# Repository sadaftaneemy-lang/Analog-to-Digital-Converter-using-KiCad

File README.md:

# Analog to Digital Converter using KiCad

## 📌 Self-Initiated Project
This is a self-initiated project created to explore and apply concepts in electronics through hands-on design and simulation

## What is KiCad ??
KiCad is a free, open-source Electronic Design Automation (EDA) tool used to design electronic circuits and Printed Circuit Boards (PCBs). 

## What is an AC to DC Converter 
An Analog to Digital Converter (ADC)  is a circuit that converts a continuous analog signal (like temperature, sound, voltage, sensor output) into a digital binary number that digital systems can process

## 🔰 Applications
An ADC is used wherever real-world analog signals must be converted into digital form for processing by digital systems like microcontrollers, DSPs, processors, or computers.

1. Audio Processing
   Microphones produce analog signals.

ADC converts:
- Voice
- Music
- Sound waves, into digital data.

Which is used  in:
- Mobile phones
- Voice recorders
- Bluetooth devices
- Digital audio systems

2. Medical equipments
  Biomedical signals are analog.

ADC is used in:
- ECG
- EEG
- Patient monitoring systems
- Digital thermometers

## 🤖 Advantages
❉ ADCs help digital systems accurately interpret continuously varying real-world signals such as temperature, sound, pressure, and light.

❉ They reduce the effect of external noise because digital signals are more reliable and less sensitive to interference than analog signals.

❉ ADCs make it possible to store analog information in digital memory devices for long-term usage and analysis.

❉ They enable fast processing of signals using microprocessors, DSPs, and embedded controllers.

❉ ADCs improve system flexibility because digital data can be easily modified, encrypted, compressed, or transmitted over networks

## 🛰️ ADC Flow
1. Analog input is applied
2. ADC samples the signal
3. Quantizes it into levels
4. Produces binary output

# 🔋 KiCad 
KiCad is an open-source EDA (Electronic Design Automation) software used for:
1. Schematic design
2. PCB layout
3. Simulation
4. Gerber generation
5. 3D PCB visualization

## 🔗🔗 Installation
I referred to this video for setup:
- [https://youtu.be/JZitbgEbCHU?si=QlpFLPeTkP8un1ju]

# 📐 About the project
This project presents the design and implementation of an AC to DC Converter PCB using KiCad. The circuit converts an alternating current (AC) input into a regulated direct current (DC) output using a bridge rectifier configuration, filtering capacitor, resistor network, and LED indication circuit.

The project was designed completely in KiCad, including:

   - Schematic design
   - PCB layout
   - Routing
   - Footprint assignment
   - Ground plane generation
   - 3D visualization preparation

This project demonstrates basic power electronics concepts along with practical PCB design workflow using an industry-standard open-source EDA tool.

## 🧩 Components Used

✮ D1–D4	1N4007 Rectifier Diodes

✮ C1	Filter Capacitor

✮ R1, R2	Resistors

✮ D5	LED Indicator

✮ J1	AC Input Terminal

✮ J2	DC Output Terminal

## 🔌 Working Principle

The AC voltage is applied through the input connector. The four diodes connected in bridge rectifier configuration convert the alternating current into pulsating DC. The capacitor filters the ripple content and provides a smoother DC output voltage. The resistor and LED combination acts as an output power indicator. The final DC output is obtained at the output terminal connector.

## 📂 Project Workflow

➤ Schematic Design

➤ ERC Verification

➤ Footprint Assignment

➤ PCB Layout Design

➤ Routing and Ground Fill

➤ DRC Check

➤ Gerber File Generation

## 🎯 Applications

⚡ Power supply circuits

⚡ Embedded systems

⚡ Educational electronics projects

⚡ PCB design practice

⚡ Low-power DC supply applications

## 🚀 Learning Outcomes

Through this project, the following concepts were learned:

- PCB designing using KiCad
- Schematic capture
- Component footprint mapping
- PCB routing techniques
- Bridge rectifier operation
- Power supply circuit fundamentals
- Design Rule Check (DRC) and ERC validation

## 📸 Project Images

**1. Schematic screenshot**

**2. PCB layout screenshot**

## Acknowledgement

This project was developed for learning and practice purposes to understand PCB design flow and AC to DC conversion using KiCad. External tutorials and documentation were referred to during installation and project development.

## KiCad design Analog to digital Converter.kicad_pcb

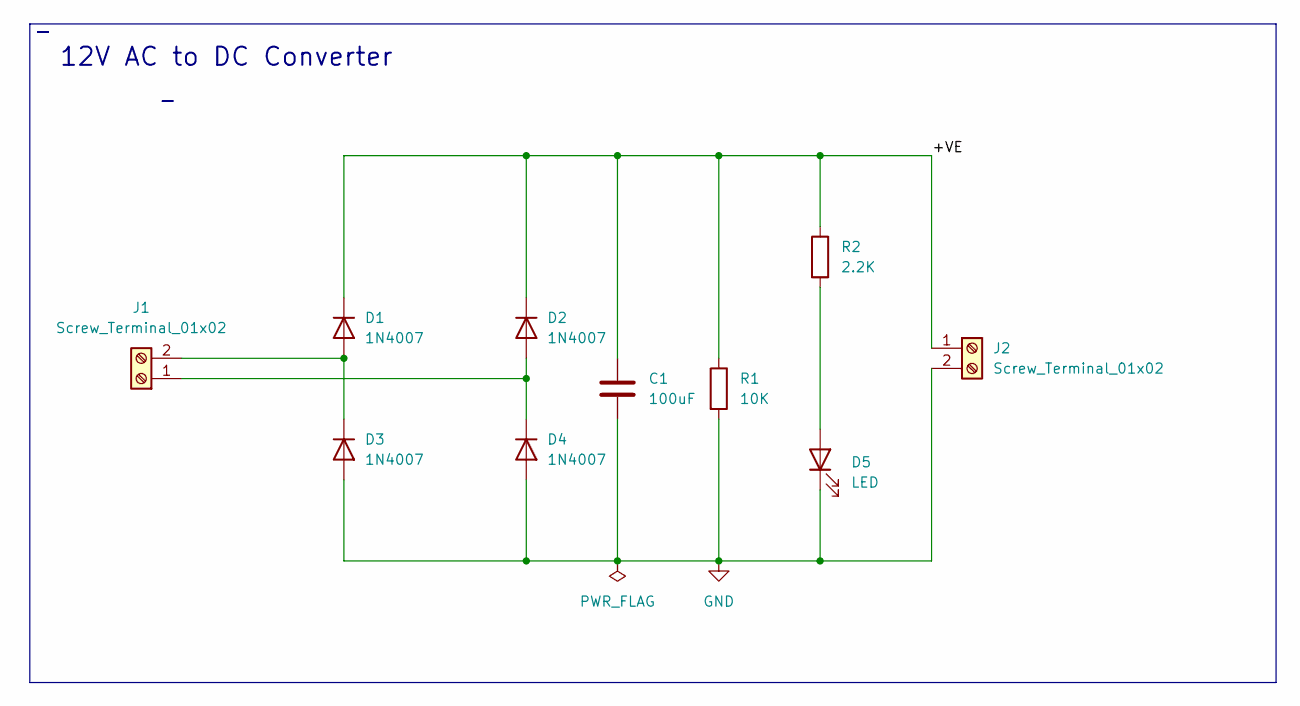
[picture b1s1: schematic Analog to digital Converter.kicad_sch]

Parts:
C1: 100uF; C_Radial_D8.0mm_H11.5mm_P3.50mm
D1, D2, D3, D4: 1N4007; D_DO-41_SOD81_P10.16mm_Horizontal
D5: LED; LED_D5.0mm
J1, J2: Screw_Terminal_01x02; TerminalBlock_MaiXu_MX126-5.0-02P_1x02_P5.00mm
R1: 10K; R_Axial_DIN0204_L3.6mm_D1.6mm_P7.62mm_Horizontal
R2: 2.2K; R_Axial_DIN0204_L3.6mm_D1.6mm_P7.62mm_Horizontal

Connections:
/+VE: C1.1, D1.1 (K), D2.1 (K), J2.1, R1.1, R2.1
GND: C1.2, D3.2 (A), D4.2 (A), D5.1 (K), J2.2, R1.2
unnamed: D1.2 (A), D3.1 (K), J1.2
unnamed: D2.2 (A), D4.1 (K), J1.1
unnamed: D5.2 (A), R2.2

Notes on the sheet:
12V AC to DC Converter

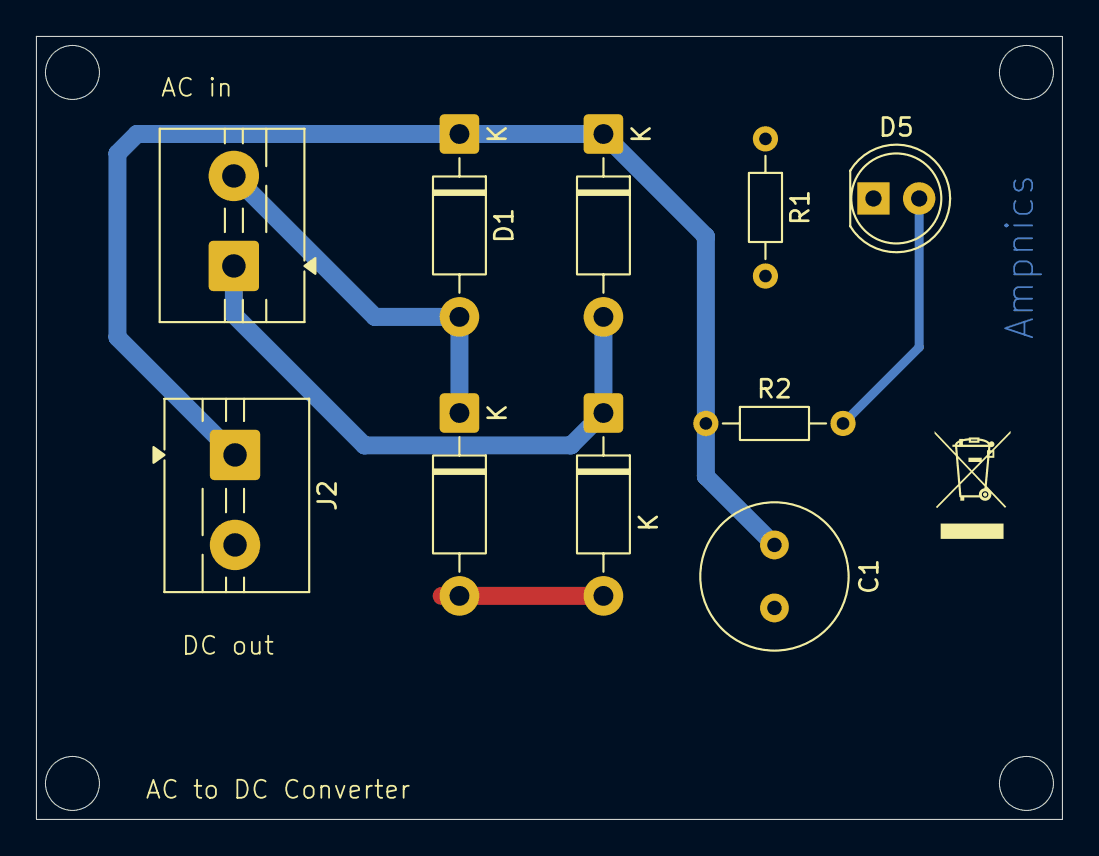
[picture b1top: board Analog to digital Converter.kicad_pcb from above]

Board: 2 copper layers, 57.0 x 43.5 mm, 10 parts (0 on the bottom side), 5 nets.

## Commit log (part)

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2026-02-03 AC to DC Converter
2026-02-03 Initialize README with project details and KiCad info
    Added project overview and introduction to KiCad and AC to DC converters.
2026-05-24 Add ADC definition to README
    Added a definition for Analog to Digital Converter (ADC) in the README.
2026-05-24 Expand README with ADC and KiCad information
    Added explanation of AC to DC converter and ADC flow.
2026-05-24 Change headings from H1 to H2 in README.md
    Updated headings in README.md to improve formatting.
2026-05-24 Revise README with ADC applications and advantages
    Updated section headers and added content about medical equipment and advantages of ADCs.
2026-05-27 Enhance README with project description and details
    Added project overview and details about the AC to DC Converter PCB design.
2026-05-28 Add components used section to README
    Added a section detailing the components used in the project.
2026-05-28 Enhance README with detailed project information
    Added sections on working principle, project workflow, applications, learning outcomes, and project images to the README.
2026-05-28 Add schematic screenshot to README
    Updated README to include schematic screenshot.
2026-05-28 Add 3D PCB view image to README
    Added a new image for the 3D PCB view.
2026-05-28 Add project workflow and applications sections to README
2026-05-28 Add acknowledgement section to README
    Added an acknowledgement section to clarify the project's purpose and sources used.
